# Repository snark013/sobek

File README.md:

# Sobek
Simple 40% ortolinear keyboard (inspired by [Plank Keyboard](https://olkb.com/collections/planck)).
Uses Pro Micro or [nrfMicro](https://github.com/joric/nrfmicro/wiki) controller (for wireless bluetooth connection).

KiCAD 3D views:

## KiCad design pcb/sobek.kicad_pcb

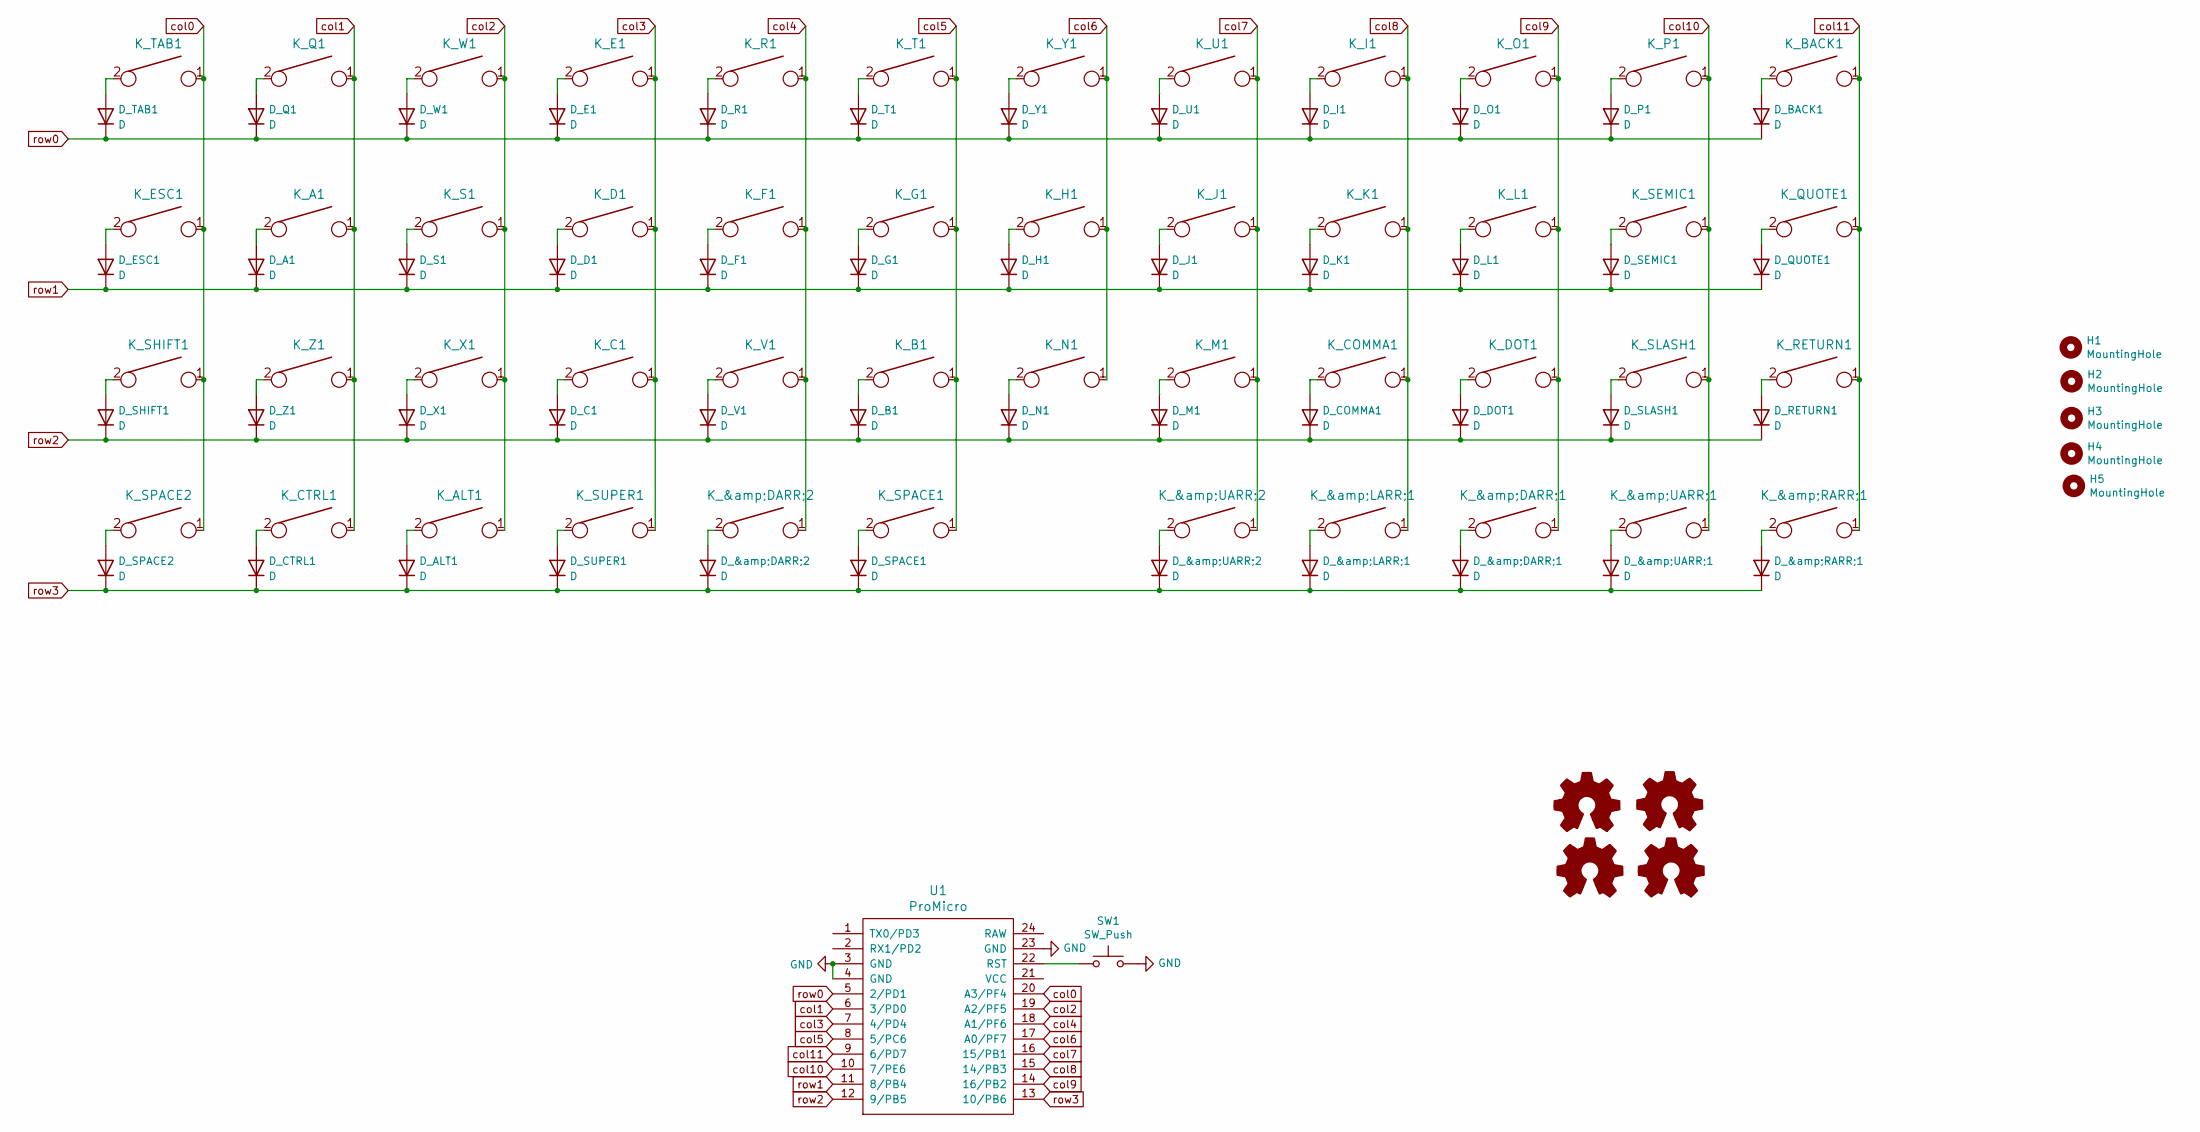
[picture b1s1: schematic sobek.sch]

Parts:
D_&amp;DARR;1, D_&amp;DARR;2: D; D_SOD123W_hand
D_&amp;LARR;1: D; D_SOD123W_hand
D_&amp;RARR;1: D; D_SOD123W_hand
D_&amp;UARR;1, D_&amp;UARR;2: D; D_SOD123W_hand
D_A1: D; D_SOD123W_hand
D_ALT1: D; D_SOD123W_hand
D_B1: D; D_SOD123W_hand
D_BACK1: D; D_SOD123W_hand
D_C1: D; D_SOD123W_hand
D_COMMA1: D; D_SOD123W_hand
D_CTRL1: D; D_SOD123W_hand
D_D1: D; D_SOD123W_hand
D_DOT1: D; D_SOD123W_hand
D_E1: D; D_SOD123W_hand
D_ESC1: D; D_SOD123W_hand
D_F1: D; D_SOD123W_hand
D_G1: D; D_SOD123W_hand
D_H1: D; D_SOD123W_hand
D_I1: D; D_SOD123W_hand
D_J1: D; D_SOD123W_hand
D_K1: D; D_SOD123W_hand
D_L1: D; D_SOD123W_hand
D_M1: D; D_SOD123W_hand
D_N1: D; D_SOD123W_hand
D_O1: D; D_SOD123W_hand
D_P1: D; D_SOD123W_hand
D_Q1: D; D_SOD123W_hand
D_QUOTE1: D; D_SOD123W_hand
D_R1: D; D_SOD123W_hand
D_RETURN1: D; D_SOD123W_hand
D_S1: D; D_SOD123W_hand
D_SEMIC1: D; D_SOD123W_hand
D_SHIFT1: D; D_SOD123W_hand
D_SLASH1: D; D_SOD123W_hand
D_SPACE1, D_SPACE2: D; D_SOD123W_hand
D_SUPER1: D; D_SOD123W_hand
D_T1: D; D_SOD123W_hand
D_TAB1: D; D_SOD123W_hand
D_U1: D; D_SOD123W_hand
D_V1: D; D_SOD123W_hand
D_W1: D; D_SOD123W_hand
D_X1: D; D_SOD123W_hand
D_Y1: D; D_SOD123W_hand
D_Z1: D; D_SOD123W_hand
H1, H2, H3, H4, H5: MountingHole; M2_HOLE_PCB
K_&amp;DARR;1, K_&amp;DARR;2: KEYSW; MX-1U-NoLED
K_&amp;LARR;1: KEYSW; MX-1U-NoLED
K_&amp;RARR;1: KEYSW; MX-1U-NoLED
K_&amp;UARR;1, K_&amp;UARR;2: KEYSW; MX-1U-NoLED
K_A1: KEYSW; MX-1U-NoLED
K_ALT1: KEYSW; MX-1U-NoLED
K_B1: KEYSW; MX-1U-NoLED
K_BACK1: KEYSW; MX-1U-NoLED
K_C1: KEYSW; MX-1U-NoLED
K_COMMA1: KEYSW; MX-1U-NoLED
K_CTRL1: KEYSW; MX-1U-NoLED
K_D1: KEYSW; MX-1U-NoLED
K_DOT1: KEYSW; MX-1U-NoLED
K_E1: KEYSW; MX-1U-NoLED
K_ESC1: KEYSW; MX-1U-NoLED
K_F1: KEYSW; MX-1U-NoLED
K_G1: KEYSW; MX-1U-NoLED
K_H1: KEYSW; MX-1U-NoLED
K_I1: KEYSW; MX-1U-NoLED
K_J1: KEYSW; MX-1U-NoLED
K_K1: KEYSW; MX-1U-NoLED
K_L1: KEYSW; MX-1U-NoLED
K_M1: KEYSW; MX-1U-NoLED
K_N1: KEYSW; MX-1U-NoLED
K_O1: KEYSW; MX-1U-NoLED
K_P1: KEYSW; MX-1U-NoLED
K_Q1: KEYSW; MX-1U-NoLED
K_QUOTE1: KEYSW; MX-1U-NoLED
K_R1: KEYSW; MX-1U-NoLED
K_RETURN1: KEYSW; MX-1U-NoLED
K_S1: KEYSW; MX-1U-NoLED
K_SEMIC1: KEYSW; MX-1U-NoLED
K_SHIFT1: KEYSW; MX-1U-NoLED
K_SLASH1: KEYSW; MX-1U-NoLED
K_SPACE1, K_SPACE2: KEYSW; MX-1U-NoLED
K_SUPER1: KEYSW; MX-1U-NoLED
K_T1: KEYSW; MX-1U-NoLED
K_TAB1: KEYSW; MX-1U-NoLED
K_U1: KEYSW; MX-1U-NoLED
K_V1: KEYSW; MX-1U-NoLED
K_W1: KEYSW; MX-1U-NoLED
K_X1: KEYSW; MX-1U-NoLED
K_Y1: KEYSW; MX-1U-NoLED
K_Z1: KEYSW; MX-1U-NoLED
LOGO1, LOGO3: Logo_Open_Hardware_Small; sphinx-logo
LOGO2, LOGO4: Logo_Open_Hardware_Small; sobek-logo
SW1: SW_Push; TACT_SWITCH_TVBP06
U1: ProMicro; ArduinoProMicro

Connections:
GND: SW1.2, U1.3 (GND), U1.4 (GND), U1.23 (GND)
unnamed: D_&amp;DARR;1.2 (A), K_&amp;DARR;1.2
unnamed: D_&amp;DARR;2.2 (A), K_&amp;DARR;2.2
unnamed: D_&amp;LARR;1.2 (A), K_&amp;LARR;1.2
unnamed: D_&amp;RARR;1.2 (A), K_&amp;RARR;1.2
unnamed: D_&amp;UARR;1.2 (A), K_&amp;UARR;1.2
unnamed: D_&amp;UARR;2.2 (A), K_&amp;UARR;2.2
unnamed: D_A1.2 (A), K_A1.2
unnamed: D_ALT1.2 (A), K_ALT1.2
unnamed: D_B1.2 (A), K_B1.2
unnamed: D_BACK1.2 (A), K_BACK1.2
unnamed: D_C1.2 (A), K_C1.2
unnamed: D_COMMA1.2 (A), K_COMMA1.2
unnamed: D_CTRL1.2 (A), K_CTRL1.2
unnamed: D_D1.2 (A), K_D1.2
unnamed: D_DOT1.2 (A), K_DOT1.2
unnamed: D_E1.2 (A), K_E1.2
unnamed: D_ESC1.2 (A), K_ESC1.2
unnamed: D_F1.2 (A), K_F1.2
unnamed: D_G1.2 (A), K_G1.2
unnamed: D_H1.2 (A), K_H1.2
unnamed: D_I1.2 (A), K_I1.2
unnamed: D_J1.2 (A), K_J1.2
unnamed: D_K1.2 (A), K_K1.2
unnamed: D_L1.2 (A), K_L1.2
unnamed: D_M1.2 (A), K_M1.2
unnamed: D_N1.2 (A), K_N1.2
unnamed: D_O1.2 (A), K_O1.2
unnamed: D_P1.2 (A), K_P1.2
unnamed: D_Q1.2 (A), K_Q1.2
unnamed: D_QUOTE1.2 (A), K_QUOTE1.2
unnamed: D_R1.2 (A), K_R1.2
unnamed: D_RETURN1.2 (A), K_RETURN1.2
unnamed: D_S1.2 (A), K_S1.2
unnamed: D_SEMIC1.2 (A), K_SEMIC1.2
unnamed: D_SHIFT1.2 (A), K_SHIFT1.2
unnamed: D_SLASH1.2 (A), K_SLASH1.2
unnamed: D_SPACE1.2 (A), K_SPACE1.2
unnamed: D_SPACE2.2 (A), K_SPACE2.2
unnamed: D_SUPER1.2 (A), K_SUPER1.2
unnamed: D_T1.2 (A), K_T1.2
unnamed: D_TAB1.2 (A), K_TAB1.2
unnamed: D_U1.2 (A), K_U1.2
unnamed: D_V1.2 (A), K_V1.2
unnamed: D_W1.2 (A), K_W1.2
unnamed: D_X1.2 (A), K_X1.2
unnamed: D_Y1.2 (A), K_Y1.2
unnamed: D_Z1.2 (A), K_Z1.2
unnamed: SW1.1, U1.22 (RST)
col0: K_ESC1.1, K_SHIFT1.1, K_SPACE2.1, K_TAB1.1, U1.20 (A3/PF4)
col1: K_A1.1, K_CTRL1.1, K_Q1.1, K_Z1.1, U1.6 (3/PD0)
col2: K_ALT1.1, K_S1.1, K_W1.1, K_X1.1, U1.19 (A2/PF5)
col3: K_C1.1, K_D1.1, K_E1.1, K_SUPER1.1, U1.7 (4/PD4)
col4: K_&amp;DARR;2.1, K_F1.1, K_R1.1, K_V1.1, U1.18 (A1/PF6)
col5: K_B1.1, K_G1.1, K_SPACE1.1, K_T1.1, U1.8 (5/PC6)
col6: K_H1.1, K_N1.1, K_Y1.1, U1.17 (A0/PF7)
col7: K_&amp;UARR;2.1, K_J1.1, K_M1.1, K_U1.1, U1.16 (15/PB1)
col8: K_&amp;LARR;1.1, K_COMMA1.1, K_I1.1, K_K1.1, U1.15 (14/PB3)
col9: K_&amp;DARR;1.1, K_DOT1.1, K_L1.1, K_O1.1, U1.14 (16/PB2)
col10: K_&amp;UARR;1.1, K_P1.1, K_SEMIC1.1, K_SLASH1.1, U1.10 (7/PE6)
col11: K_&amp;RARR;1.1, K_BACK1.1, K_QUOTE1.1, K_RETURN1.1, U1.9 (6/PD7)
row0: D_BACK1.1 (K), D_E1.1 (K), D_I1.1 (K), D_O1.1 (K), D_P1.1 (K), D_Q1.1 (K), D_R1.1 (K), D_T1.1 (K), D_TAB1.1 (K), D_U1.1 (K), D_W1.1 (K), D_Y1.1 (K), U1.5 (2/PD1)
row1: D_A1.1 (K), D_D1.1 (K), D_ESC1.1 (K), D_F1.1 (K), D_G1.1 (K), D_H1.1 (K), D_J1.1 (K), D_K1.1 (K), D_L1.1 (K), D_QUOTE1.1 (K), D_S1.1 (K), D_SEMIC1.1 (K), U1.11 (8/PB4)
row2: D_B1.1 (K), D_C1.1 (K), D_COMMA1.1 (K), D_DOT1.1 (K), D_M1.1 (K), D_N1.1 (K), D_RETURN1.1 (K), D_SHIFT1.1 (K), D_SLASH1.1 (K), D_V1.1 (K), D_X1.1 (K), D_Z1.1 (K), U1.12 (9/PB5)
row3: D_&amp;DARR;1.1 (K), D_&amp;DARR;2.1 (K), D_&amp;LARR;1.1 (K), D_&amp;RARR;1.1 (K), D_&amp;UARR;1.1 (K), D_&amp;UARR;2.1 (K), D_ALT1.1 (K), D_CTRL1.1 (K), D_SPACE1.1 (K), D_SPACE2.1 (K), D_SUPER1.1 (K), U1.13 (10/PB6)

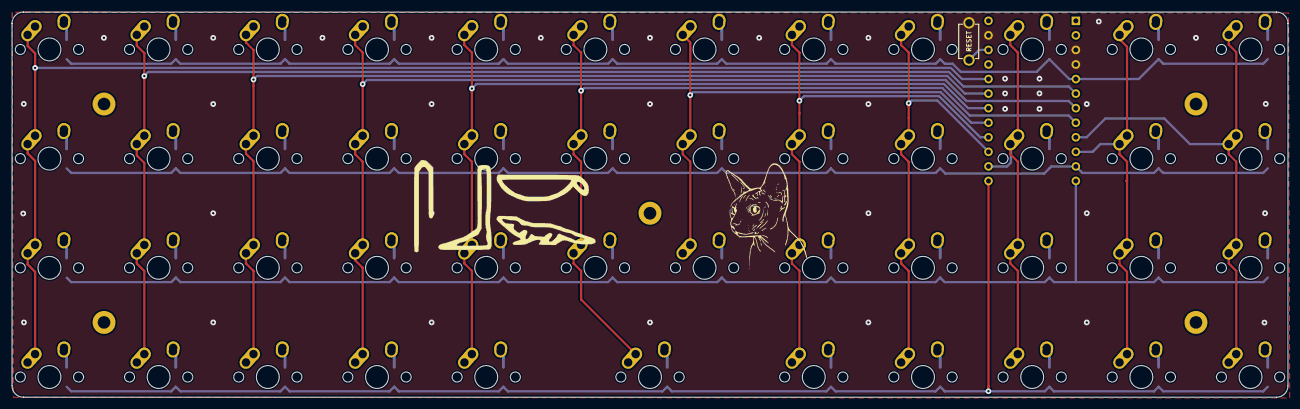
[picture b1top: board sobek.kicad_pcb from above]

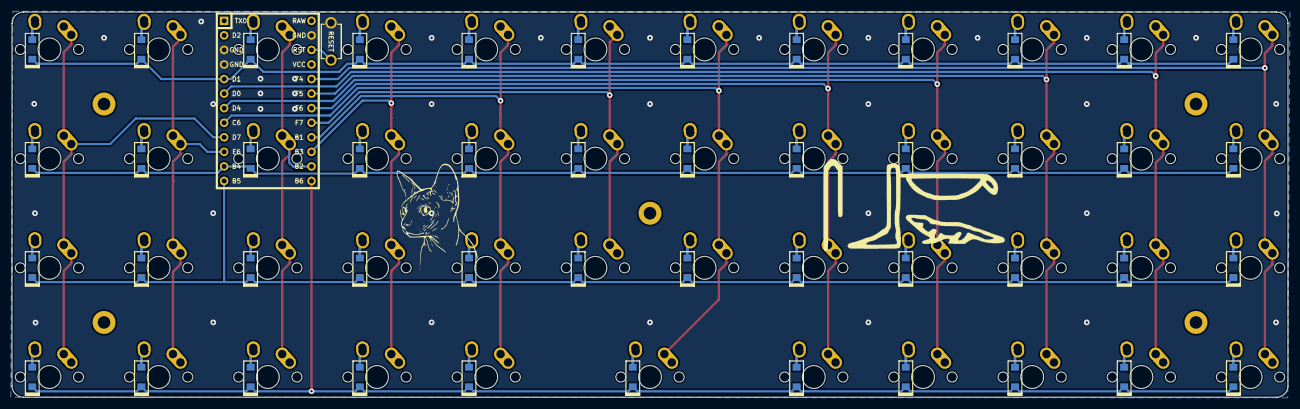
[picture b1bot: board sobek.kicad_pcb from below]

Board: 2 copper layers, 222.6 x 67.2 mm, 105 parts (50 on the bottom side), 65 nets.

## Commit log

2021-08-29 ChangeLog: - initial release.
2021-08-29 ChangeLog: - remove unnecessary info from board.
2021-08-30 ChangeLog: KiCAD images added.
